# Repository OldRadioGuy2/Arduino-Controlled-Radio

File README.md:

# Arduino-Controlled-Radio
An Arduino Controlled SI47xx Radio

This repository contains code and hardware design for an Arduino controlled radio based on the Skyworks SI47xx series of integrated radios, particularly the SI4735.

This particular implementation was concieved as a "behind the scenes" replacement for antique radio chassis that are too far gone for refurbishing. The idea is to use the Arduino to "read" the radio's original controls and translate their volume, tuning, and band settings to the SI chip. An NE55C is used to translate the tuning capacitor setting to a pulse width. A BLE Bluetooth module is included so that configuration, calibration, and remote control can be done using a smartphone application. Finally, the audio output is buffered for stero headphone use or amplified using an on-board LM1875 to drive a speaker.

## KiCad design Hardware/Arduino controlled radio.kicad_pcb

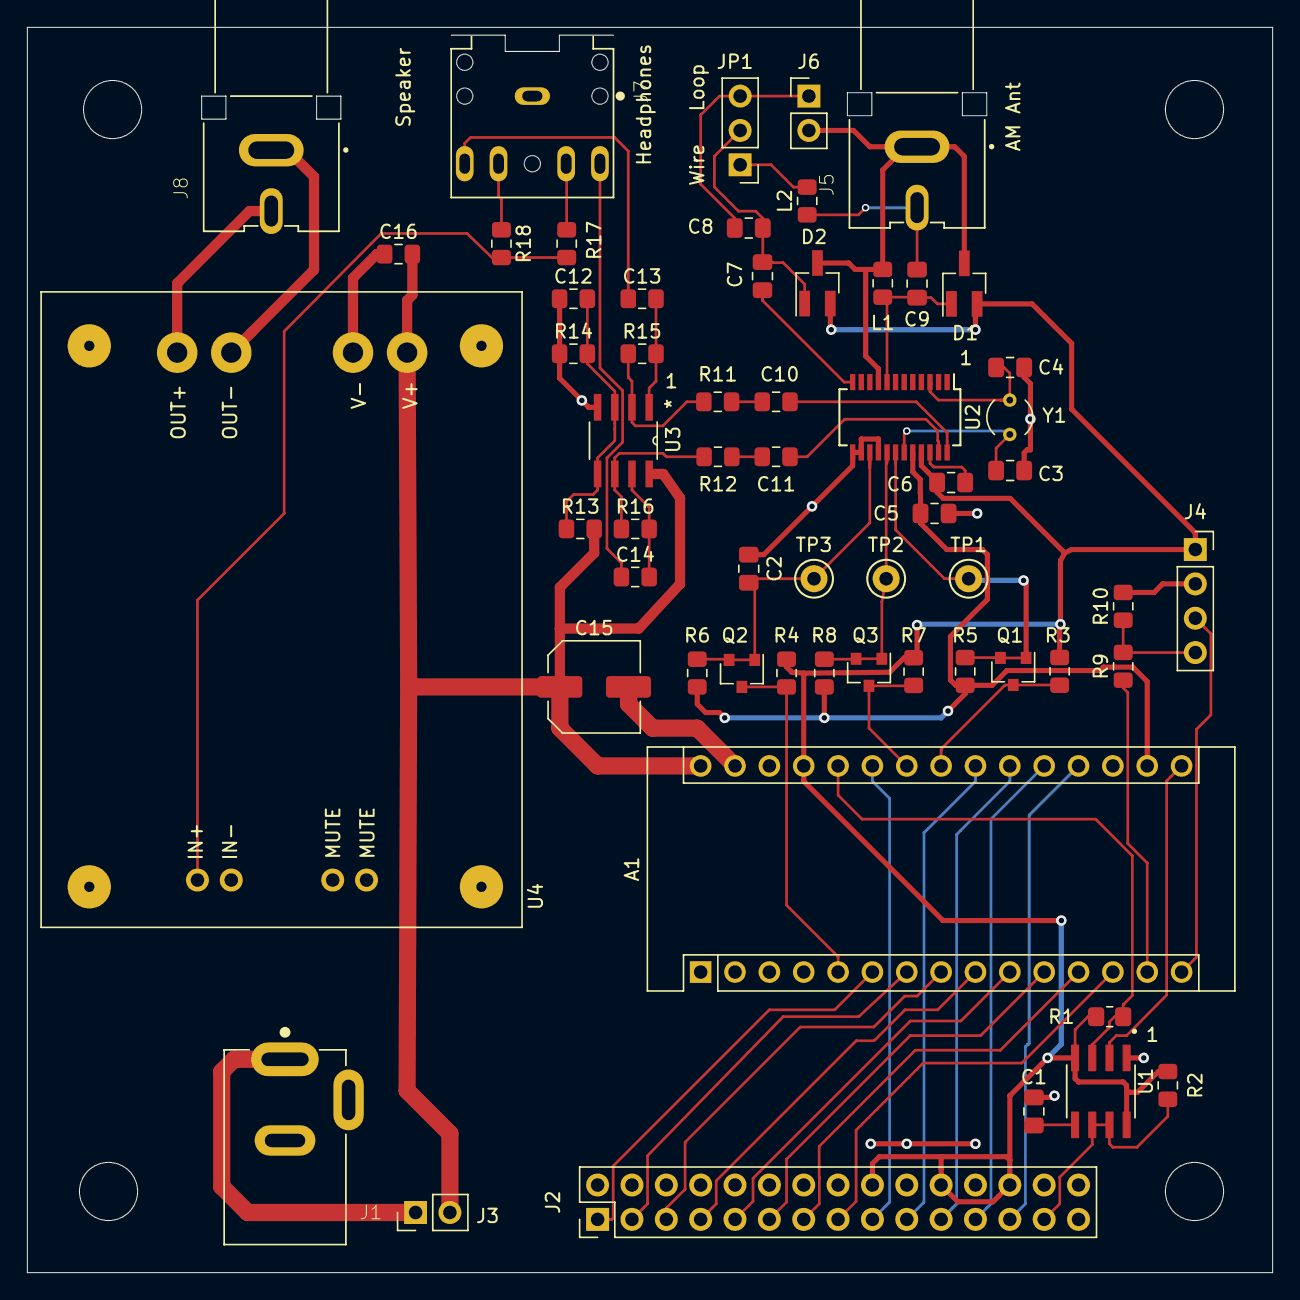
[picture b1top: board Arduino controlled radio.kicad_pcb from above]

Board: 2 copper layers, 92.1 x 92.1 mm, 59 parts (0 on the bottom side), 57 nets.

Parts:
A1: Arduino_BLE_Nano; Arduino_Nano
C1: .01uF; C_0805_2012Metric_Pad1.18x1.45mm_HandSolder
C2: 10nF; C_0805_2012Metric_Pad1.18x1.45mm_HandSolder
C3, C4: 22pf; C_0805_2012Metric_Pad1.18x1.45mm_HandSolder
C5: 100nf; C_0805_2012Metric_Pad1.18x1.45mm_HandSolder
C6: 22nf; C_0805_2012Metric_Pad1.18x1.45mm_HandSolder
C7: .47uF; C_0805_2012Metric_Pad1.18x1.45mm_HandSolder
C8: 33pF; C_0805_2012Metric_Pad1.18x1.45mm_HandSolder
C9: 6.8pF; C_0805_2012Metric_Pad1.18x1.45mm_HandSolder
C10, C11: 1uF; C_0805_2012Metric_Pad1.15x1.40mm_HandSolder
C12: .1uF; C_0805_2012Metric_Pad1.15x1.40mm_HandSolder
C13, C14: 10uF; C_0805_2012Metric_Pad1.15x1.40mm_HandSolder
C15: 100uF; C_Elec_6.3x5.4
C16: .1 uF; C_0805_2012Metric_Pad1.15x1.40mm_HandSolder
D1, D2: CM1213A-01SO; SOT-23_Handsoldering
J1: Jack-DC; CUI_PJ-202B
J2: Conn_02x15_Odd_Even; PinHeader_2x15_P2.54mm_Vertical
J3, J6: Conn_01x02; PinHeader_1x02_P2.54mm_Vertical
J4: HC-06 Connector; PinSocket_1x04_P2.54mm_Vertical
J5: Conn_Coaxial; CUI_RCJ-045
J7: SJ1-3525NG; CUI_SJ1-3525NG
J8: Speaker; CUI_RCJ-045
JP1: Ext/Loop Antenna; PinHeader_1x03_P2.54mm_Vertical
L1: 150nH; L_0805_2012Metric_Pad1.15x1.40mm_HandSolder
L2: 4.7uH; L_0805_2012Metric_Pad1.15x1.40mm_HandSolder
Q1, Q2, Q3: 2N7002; SOT-23
R1: 2.2k; R_0805_2012Metric_Pad1.20x1.40mm_HandSolder
R2: 1Meg; R_0805_2012Metric_Pad1.15x1.40mm_HandSolder
R3, R4, R5, R6, R7, R8: 10K; R_0805_2012Metric_Pad1.15x1.40mm_HandSolder
R9: 2.2K; R_0805_2012Metric_Pad1.15x1.40mm_HandSolder
R10: 3.8K; R_0805_2012Metric_Pad1.15x1.40mm_HandSolder
R11, R12, R13, R14, R15, R16: 22K; R_0805_2012Metric_Pad1.15x1.40mm_HandSolder
R17, R18: 1K; R_0805_2012Metric_Pad1.15x1.40mm_HandSolder
TP1, TP2, TP3: TestPoint; TestPoint_Keystone_5000-5004_Miniature
U1: NE555; SOIC-8N
U2: Si4735-D60-GU; SSOP-24_3.9x8.7mm_P0.635mm
U3: LM358; TL082CDR
U4: TPA3118AmplifierBoard; TPA3118_Board
Y1: 32768KHz; Crystal_AT310_D3.0mm_L10.0mm_Vertical

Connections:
+3V3: A1.17, C5.1, R5.1, R6.1, R8.1, U2.20
+5V: A1.27, C6.2, D1.2, D2.2, J2.18, J2.22, J2.26, J4.1, R1.1, R2.1, R3.1, R4.1, R7.1, U1.4, U1.8, U2.21
+12V: A1.30, C15.1, C16.2, J3.2, R13.2, U3.8, U4.5
GNDA: D1.3, D2.3, J5.2, J6.2, L1.2, U2.9
GNDREF: A1.4, A1.29, C1.1, C2.2, C3.2, C4.2, C5.2, C12.1, C15.2, C16.1, J1.2, J2.2, J2.4, J2.6, J2.8, J2.10, J2.12, J2.14, J2.16, J2.20, J2.24, J2.28, J2.29, J2.30, J4.2, J7.1, R10.2, R14.1, U1.1, U2.13, U2.14, U2.16, U3.4, U4.2, U4.6
HC-06RxD: A1.15, J4.3
HC-06TxD: A1.14, R9.1
LChan: C11.2, U2.23
unnamed: A1.5, Q2.3, R4.2
unnamed: A1.6, J2.1
unnamed: A1.7, J2.3
unnamed: A1.8, J2.5
unnamed: A1.9, J2.7
unnamed: A1.10, J2.9
unnamed: A1.11, J2.11
unnamed: A1.12, J2.13
unnamed: A1.13, J2.15
unnamed: A1.16, U1.2
unnamed: A1.19, J2.25
unnamed: A1.20, J2.23
unnamed: A1.21, J2.21
unnamed: A1.22, J2.19
unnamed: A1.23, Q1.3, R3.2
unnamed: A1.24, Q3.3, R7.2
unnamed: A1.25, J2.17
unnamed: A1.26, R1.2, U1.3
unnamed: C1.2, U1.5
unnamed: C2.1, Q2.1, Q2.2, R6.2, TP3.1, U2.15
unnamed: C3.1, U2.19, Y1.1
unnamed: C4.1, U2.3, Y1.2
unnamed: C6.1, U2.22
unnamed: C7.1, C8.2, D2.1, JP1.2
unnamed: C7.2, U2.12
unnamed: C8.1, J6.1, JP1.3
unnamed: C9.1, J5.1, L2.1
unnamed: C9.2, D1.1, L1.1, U2.8
unnamed: C10.1, R11.1
unnamed: C11.1, R12.1
unnamed: C12.2, R13.1, R14.2, U3.3, U3.5
unnamed: C13.1, J7.2
unnamed: C13.2, R15.2, U3.1
unnamed: C14.1, J7.3
unnamed: C14.2, R16.2, U3.7
unnamed: J1.1, J3.1
unnamed: J2.27, R2.2, U1.6, U1.7
unnamed: J4.4, R9.2, R10.1
unnamed: J7.4, R18.1
unnamed: J7.5, R17.1
unnamed: J8.1, U4.7
unnamed: J8.2, U4.8
unnamed: JP1.1, L2.2
unnamed: Q1.1, Q1.2, R5.2, TP1.1, U2.18
unnamed: Q3.1, Q3.2, R8.2, TP2.1, U2.17
unnamed: R11.2, R15.1, U3.2
unnamed: R12.2, R16.1, U3.6
unnamed: R17.2, R18.2, U4.1
RChan: C10.2, U2.24

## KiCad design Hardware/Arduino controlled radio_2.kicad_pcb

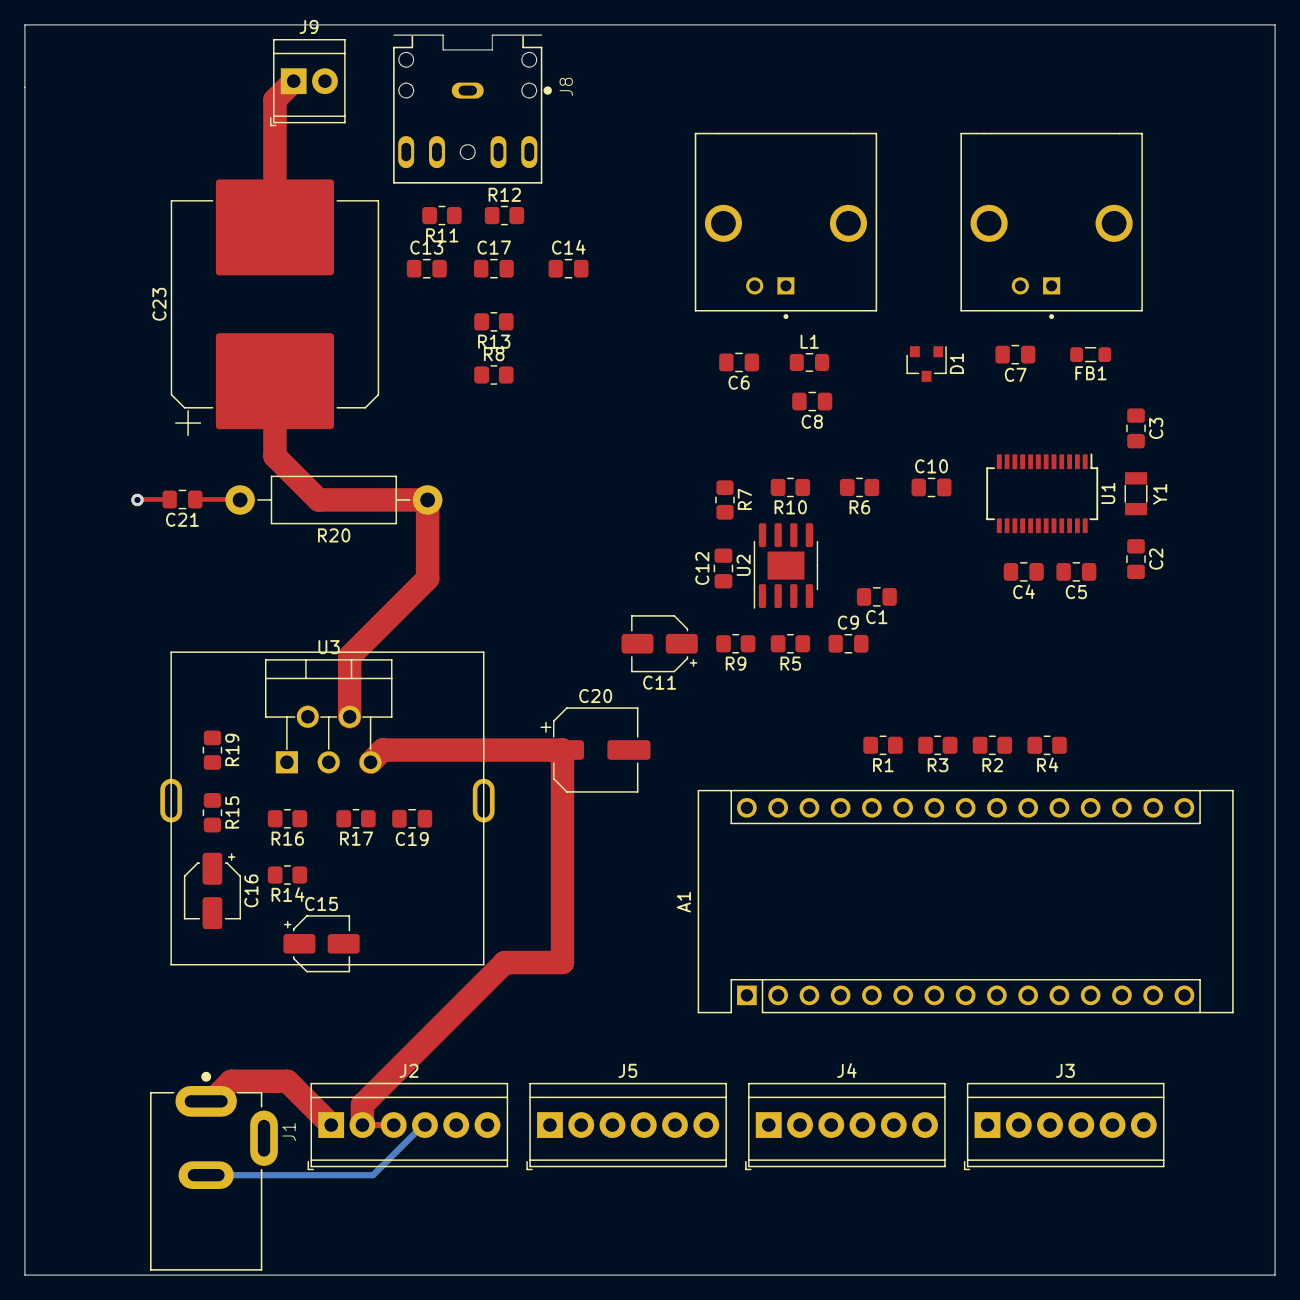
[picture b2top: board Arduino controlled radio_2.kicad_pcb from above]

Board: 2 copper layers, 101.6 x 101.6 mm, 57 parts (0 on the bottom side), 48 nets.

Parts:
A1: Arduino_BLE_Nano; Arduino_Nano
C1: 10nF; C_0805_2012Metric_Pad1.18x1.45mm_HandSolder
C2, C3: 22pf; C_0805_2012Metric_Pad1.18x1.45mm_HandSolder
C4: 100nf; C_0805_2012Metric_Pad1.18x1.45mm_HandSolder
C5: 22nf; C_0805_2012Metric_Pad1.18x1.45mm_HandSolder
C6, C8: 3.3pF; C_0805_2012Metric_Pad1.18x1.45mm_HandSolder
C7: 6.8pF; C_0805_2012Metric_Pad1.18x1.45mm_HandSolder
C9, C10, C12, C13, C14, C19: .1uF; C_0805_2012Metric_Pad1.18x1.45mm_HandSolder
C11, C15, C16: 10uF 16V; CP_Elec_4x5.3
C17: 1uF; C_0805_2012Metric_Pad1.18x1.45mm_HandSolder
C20: 100uF 50V; CP_Elec_6.3x7.7
C21: .22uF; C_0805_2012Metric_Pad1.18x1.45mm_HandSolder
C23: 2200uF 16V; CP_Elec_16x17.5
D1: SP0502BAHT; SOT-23
FB1: Ferrite_Bead_Small; L_0805_2012Metric_Pad1.05x1.20mm_HandSolder
J1: Jack-DC; CUI_PJ-202B
J2, J3, J4, J5: Screw_Terminal_01x06; TerminalBlock_TE_282834-6_1x06_P2.54mm_Horizontal
J6, J7: Conn_Coaxial; CONN_1-1337543-0
J8: SJ1-3525NG; CUI_SJ1-3525NG
J9: Screw_Terminal_01x02; TerminalBlock_TE_282834-2_1x02_P2.54mm_Horizontal
L1: 10nH; L_0805_2012Metric_Pad1.15x1.40mm_HandSolder
R1: 10k; R_0805_2012Metric_Pad1.20x1.40mm_HandSolder
R2, R3, R15: 4.7K; R_0805_2012Metric_Pad1.20x1.40mm_HandSolder
R4: 10K; R_0805_2012Metric_Pad1.20x1.40mm_HandSolder
R5, R6, R7, R8, R14, R16, R17: 22K; R_0805_2012Metric_Pad1.20x1.40mm_HandSolder
R9, R10: 220K; R_0805_2012Metric_Pad1.20x1.40mm_HandSolder
R11, R12: 470; R_0805_2012Metric_Pad1.20x1.40mm_HandSolder
R13: 1Meg; R_0805_2012Metric_Pad1.20x1.40mm_HandSolder
R19: 470K; R_0805_2012Metric_Pad1.20x1.40mm_HandSolder
R20: 1ohm 1.2W; R_Axial_DIN0411_L9.9mm_D3.6mm_P15.24mm_Horizontal
U1: Si4735-D60-GU; SSOP-24_3.9x8.7mm_P0.635mm
U2: LM358; SOIC-8-1EP_3.9x4.9mm_P1.27mm_EP2.29x3mm
U3: LM1875; TO-220-5_P3.4x3.7mm_StaggerOdd_Lead3.8mm_Vertical
Y1: 32768KHz; Crystal_SMD_3215-2Pin_3.2x1.5mm

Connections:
12V: A1.30, C12.2, C19.2, C20.1, J2.2, J2.3, J2.5, R7.2, R17.1, U2.8, U3.5
+5V: A1.27, C5.2, J4.3, J5.1, J5.4, U1.21
GNDREF: A1.4, A1.29, C1.2, C2.2, C3.2, C4.2, C11.2, C12.1, C15.2, C16.2, C19.1, C20.2, C21.2, D1.3, J1.2, J2.4, J2.6, J3.6, J4.2, J4.5, J4.6, J5.3, J5.6, J8.1, J9.2, R8.1, R13.2, R14.2, U1.13, U1.14, U2.4, U3.3
LChan: C10.2, U1.23
unnamed: A1.9, R4.2
unnamed: A1.10, J3.1
unnamed: A1.11, J3.2
unnamed: A1.12, J3.3
unnamed: A1.13, J3.4
unnamed: A1.14, J3.5
unnamed: A1.15, R1.1
unnamed: A1.16, A1.26, J4.1, R1.2
unnamed: A1.17, C4.1, R2.1, R3.1, U1.20
unnamed: A1.21, J5.5
unnamed: A1.22, J5.2
unnamed: A1.23, R2.2, U1.18
unnamed: A1.24, R3.2, U1.17
unnamed: A1.25, J4.4
unnamed: C1.1, R4.1, U1.15
unnamed: C2.1, U1.19, Y1.1
unnamed: C3.1, U1.3, Y1.2
unnamed: C5.1, U1.22
unnamed: C6.1, L1.1, U1.12
unnamed: C6.2, C7.2, C8.2, J6.2, J7.2, U1.9
unnamed: C7.1, FB1.2, U1.8
unnamed: C8.1, D1.2, J6.1, L1.2
unnamed: C9.1, R5.1
unnamed: C10.1, R6.1
unnamed: C11.1, R7.1, R8.2, U2.3, U2.5
unnamed: C13.1, J8.2
unnamed: C13.2, R9.2, U2.1
unnamed: C14.1, J8.3
unnamed: C14.2, R10.2, U2.7
unnamed: C15.1, R14.1, R16.1, R17.2
unnamed: C16.1, R15.2
unnamed: C17.1, R16.2, U3.1
unnamed: C17.2, R11.1, R12.1, R13.1
unnamed: C21.1, R20.2
unnamed: C23.1, R19.1, R20.1, U3.4
unnamed: C23.2, J9.1
unnamed: D1.1, FB1.1, J7.1
unnamed: J1.1, J2.1
unnamed: J8.4, R11.2
unnamed: J8.5, R12.2
unnamed: R5.2, R9.1, U2.2
unnamed: R6.2, R10.1, U2.6
unnamed: R15.1, R19.2, U3.2
RChan: C9.2, U1.24

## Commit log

2022-03-05 Created
2022-03-09 Temporarily comment out functions
2022-03-16 Initial Upload
2022-03-16 Forgot the .md extension
2022-03-30 Set up command processor structures.
2022-04-03 Added config, fleshed out the basics in main
2022-04-12 Added selective build app or test program.
2022-04-25 Delete 2743021447.pdf
    Not part of build
2022-04-25 Rev 3 Boards
2022-05-13 still trying
2022-07-19 Initial commit of PC software
2022-07-20 Initial upload of PC Client
2022-07-20 Simplified
2022-07-20 Added additional directory
2022-07-20 Added Dist
2022-07-20 Config and radio working
2022-08-09 Added Serial I/O; Each band now has current frequency
2022-08-09 Adding new Project
2022-08-09 Updated .gitignore
2022-08-30 Added configuration dialog
2022-08-30 Changed "configuration" to "Db" to clarify configuration functions from stored data
2022-09-06 Added Band and db saves to config dialog
2022-09-06 Add GFX
2022-09-06 Ability to re-draw Freq.
2022-09-07 switch back to the ATMega processor, not my BLE Nano.
2022-09-28 fix MAX Volume, add an analog reference.
2022-10-05 Add a second serial implementation for BLE.
2022-10-17 move towards new spec, calibration, band configuration not implemented.
2022-10-26 add a buffer for outputting numbers, connect it to some get-functions.
2022-11-16 don't compile these files unless selected.
2022-12-28 Band is now 0 - 3 and can be AM, FM, so-on. Code to save parts of the configuration need to be added next.
2023-01-10 create band, other commands write their configuration.
2023-01-10 don't set frequency if the mode isn't valid
2023-01-11 fix some last side-effects, like setting a valid freq when it had not been valid.
2023-01-18 Finish the one's base for band, only fail one time.
2023-01-20 Radio stops working when config grows past 3, extra check in load_config()
2023-02-15 use F() to put string constants into text.
2023-02-15 Num Bands increased to 5. F() used in commands.cpp and config.cpp Display support is enabled, send "ED,1" to enable drawing.
2023-02-21 Get signal level connected to radio library.
2023-03-06 First pass for calibration, needs to be tested with external hw.
2023-03-18 some return values to commands
2023-03-28 attempt at log scaling for volume
2023-03-29 first pass of frequency scaling
2023-05-17 debugging band switch implementation, EEPROM issues
2023-05-30 minor band switch work
2023-05-30 Ooops.
2023-05-31 always print analog val in Cal Band.
2023-06-06 working on the tuning cap feature

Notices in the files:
parts and their libraries:
Copyright 2021 Accelerated Designs. All rights reserved.
